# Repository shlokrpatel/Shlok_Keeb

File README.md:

# Shlok_Keeb
FOR SUBMISSION PURPOSES- here is the link to my project that I completely recorded with lapse- https://lapse.hackclub.com/user/@shlok_r_patel10

a custom keyboard I built myself. This includes the pcb, case, firmware, and eventually, the assembly. I built this to learn more on how to design pcb's and get better at CAD

Built as part of Hackclub's YSWS Keeb

# Features
Custom pcb made in kicad
MX switches
Qmk software
3d printed case
Individually lit rgbs for each key
Rotary Encoder
Oled Screen

# Why I build it
I love building things on my computer and seeing them come to life as I build it. I've been working at getting better at using CAD so whenever I have a chance to improve them with another skill I always take it. 

I was able to learn how to use Kicad, CAD, some firmware use, how to solder, and the engineering behind keyboard

# Design Process
I started in Kicad, I modeled the schematic with all my keys, leds, the microcontroller, oled, and rotary encoder. Then I moved to the actually pcb routing the traces, and placing the keys where i wanted them. After finished that I went to onshape to design the case in 2 peices that will be screwed or glued together. After that I went to the qmk software to write the firmware. 

# Components
Custom PCB
Raspberri pi pico
MX switches
Stabilizers
Usb cable
3D printed case
keycaps
Sk6812 Mini-e LEDs
EC11 rotary encoder
0.91in OLED display

# Challenges
My biggest challenges were:

Learned onshape 
routing my pcb with all the traces
building my case 
writing the firmware

# Images

Matrix schematic

PCB

Case

Bill of Materials(BOM)
| SI No. | Name | Notes | Quantity | Price/Unit (USD) | Total (USD) | Running Total (USD) | Link |
| --- | --- | --- | --- | --- | --- | --- | --- |
| 1 | 0.91" OLED Display | 128x32 I2C OLED, GND-VCC-SCL-SDA | 1 | $1.09 | $1.09 | $1.09 | https://www.aliexpress.us/item/2251832650376908.html |
| 2 | EC11 Rotary Encoder | ALPS EC11E compatible, vertical, H20mm | 1 | $0.46 | $0.46 | $1.55 | https://www.alibaba.com/product-detail/EC11-rotary-15-20mm-Meihua-Bing_1600985459709.html |
| 3 | Key Switches | MX compatible switches, pack of 10 | 7 | $1.00 | $7.00 | $8.55 | https://www.aliexpress.us/item/3256802192387196.html |
| 4 | SK6812MINI-E | Addressable RGB LED, LCSC C5149201 | 61 | $0.0649 | $3.96 | $12.51 | https://www.lcsc.com/product-detail/C5149201.html |
| 5 | 1N4148 Diodes | 1N4148, pack of 100 | 1 | $0.99 | $0.99 | $13.50 | https://www.aliexpress.com/w/wholesale-diode-1n4148.html |
| 6 | Durock V2 Screw-In Stabilizers | 5 stabilizers | 1 | $16.00 | $16.00 | $29.50 | https://upgradekeyboards.com/products/durock-v2-new-screw-in-stabilizers-clear |
| 7 | Custom PCB | JLCPCB manufactured PCB | 1 | $24.00 | $24.00 | $53.50 | https://jlcpcb.com/ |
| 8 | Thock King Shine Through Black PBT Keycap Set | Black pudding PBT, 61-key, RGB shine-through | 1 | $16.95 | $16.95 | $70.45 | https://www.thockking.com/products/shine-through-black-pbt-keycap-set-61-78-87-96-100-104-108 |
| 9 | Raspberry Pi Pico | RP2040 microcontroller | 1 | $4.00 | $4.00 | $74.45 | https://www.raspberrypi.com/products/raspberry-pi-pico/ |

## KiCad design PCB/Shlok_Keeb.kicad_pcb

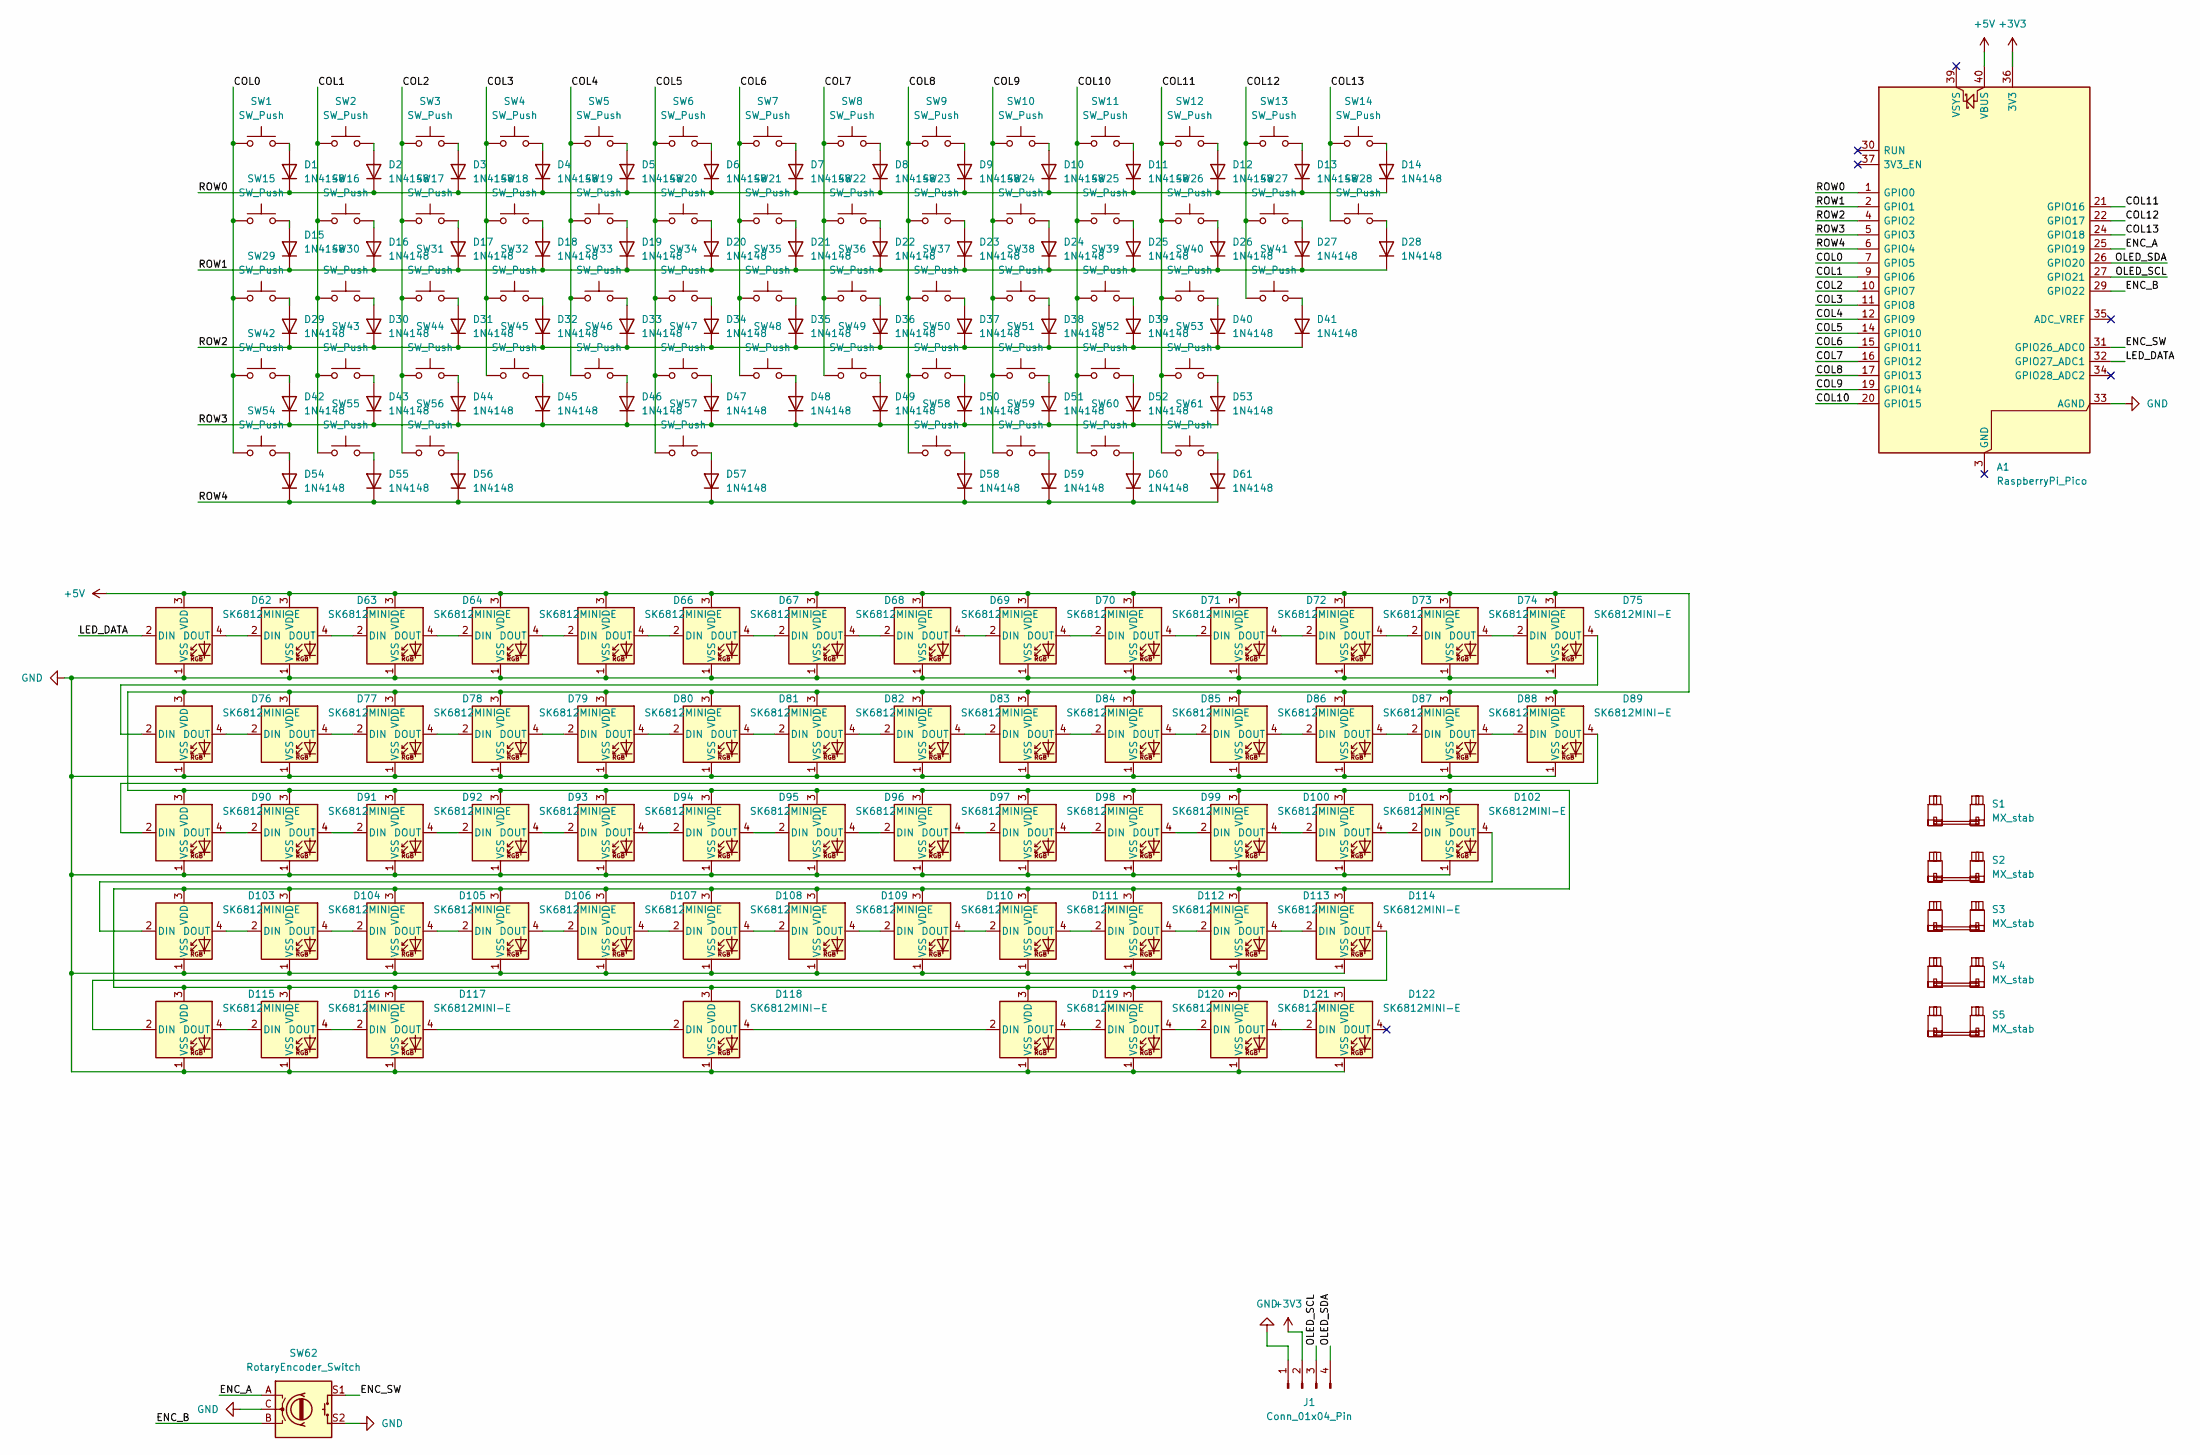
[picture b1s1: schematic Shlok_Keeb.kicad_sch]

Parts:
A1: RaspberryPi_Pico; RaspberryPi_Pico_Common_THT
D1, D2, D3, D4, D5, D6, D7, D8, D9, D10, D11, D12, D13, D14, D15, D16, D17, D18, D19, D20, D21, D22, D23, D24, D25, D26, D27, D28, D29, D30, D31, D32, D33, D34, D35, D36, D37, D38, D39, D40, D41, D42, D43, D44, D45, D46, D47, D48, D49, D50, D51, D52, D53, D54, D55, D56, D57, D58, D59, D60, D61: 1N4148; D_DO-35_SOD27_P7.62mm_Horizontal
D62, D63, D64, D65, D66, D67, D68, D69, D70, D71, D72, D73, D74, D75, D76, D77, D78, D79, D80, D81, D82, D83, D84, D85, D86, D87, D88, D89, D90, D91, D92, D93, D94, D95, D96, D97, D98, D99, D100, D101, D102, D103, D104, D105, D106, D107, D108, D109, D110, D111, D112, D113, D114, D115, D116, D117, D118, D119, D120, D121, D122: SK6812MINI-E; SK6812MINI-E_fixed
J1: Conn_01x04_Pin; ER_OLEDM0.91_1x-I2C
S1: MX_stab; STAB_MX_P_6.25u
S2, S3, S4, S5: MX_stab; STAB_MX_P_2u
SW1, SW2, SW3, SW4, SW5, SW6, SW7, SW8, SW9, SW10, SW11, SW12, SW13, SW14, SW15, SW16, SW17, SW18, SW19, SW20, SW21, SW22, SW23, SW24, SW25, SW26, SW27, SW28, SW29, SW30, SW31, SW32, SW33, SW34, SW35, SW36, SW37, SW38, SW39, SW40, SW41, SW42, SW43, SW44, SW45, SW46, SW47, SW48, SW49, SW50, SW51, SW52, SW53, SW54, SW55, SW56, SW57, SW58, SW59, SW60, SW61: SW_Push; SW_MX_1u
SW62: RotaryEncoder_Switch; RotaryEncoder_Alps_EC11E-Switch_Vertical_H20mm

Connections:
+3V3: A1.36 (3V3), J1.2
+5V: A1.40 (VBUS), D62.3 (VDD), D63.3 (VDD), D64.3 (VDD), D65.3 (VDD), D66.3 (VDD), D67.3 (VDD), D68.3 (VDD), D69.3 (VDD), D70.3 (VDD), D71.3 (VDD), D72.3 (VDD), D73.3 (VDD), D74.3 (VDD), D75.3 (VDD), D76.3 (VDD), D77.3 (VDD), D78.3 (VDD), D79.3 (VDD), D80.3 (VDD), D81.3 (VDD), D82.3 (VDD), D83.3 (VDD), D84.3 (VDD), D85.3 (VDD), D86.3 (VDD), D87.3 (VDD), D88.3 (VDD), D89.3 (VDD), D90.3 (VDD), D91.3 (VDD), D92.3 (VDD), D93.3 (VDD), D94.3 (VDD), D95.3 (VDD), D96.3 (VDD), D97.3 (VDD), D98.3 (VDD), D99.3 (VDD), D100.3 (VDD), D101.3 (VDD), D102.3 (VDD), D103.3 (VDD), D104.3 (VDD), D105.3 (VDD), D106.3 (VDD), D107.3 (VDD), D108.3 (VDD), D109.3 (VDD), D110.3 (VDD), D111.3 (VDD), D112.3 (VDD), D113.3 (VDD), D114.3 (VDD), D115.3 (VDD), D116.3 (VDD), D117.3 (VDD), D118.3 (VDD), D119.3 (VDD), D120.3 (VDD), D121.3 (VDD), D122.3 (VDD)
/COL0: A1.7 (GPIO5), SW1.1, SW15.1, SW29.1, SW42.1, SW54.1
/COL1: A1.9 (GPIO6), SW2.1, SW16.1, SW30.1, SW43.1, SW55.1
/COL2: A1.10 (GPIO7), SW3.1, SW17.1, SW31.1, SW44.1, SW56.1
/COL3: A1.11 (GPIO8), SW4.1, SW18.1, SW32.1, SW45.1
/COL4: A1.12 (GPIO9), SW5.1, SW19.1, SW33.1, SW46.1
/COL5: A1.14 (GPIO10), SW6.1, SW20.1, SW34.1, SW47.1, SW57.1
/COL6: A1.15 (GPIO11), SW7.1, SW21.1, SW35.1, SW48.1
/COL7: A1.16 (GPIO12), SW8.1, SW22.1, SW36.1, SW49.1
/COL8: A1.17 (GPIO13), SW9.1, SW23.1, SW37.1, SW50.1, SW58.1
/COL9: A1.19 (GPIO14), SW10.1, SW24.1, SW38.1, SW51.1, SW59.1
/COL10: A1.20 (GPIO15), SW11.1, SW25.1, SW39.1, SW52.1, SW60.1
/COL11: A1.21 (GPIO16), SW12.1, SW26.1, SW40.1, SW53.1, SW61.1
/COL12: A1.22 (GPIO17), SW13.1, SW27.1, SW41.1
/COL13: A1.24 (GPIO18), SW14.1, SW28.1
/ENC_A: A1.25 (GPIO19), SW62.A
/ENC_B: A1.29 (GPIO22), SW62.B
/ENC_SW: A1.31 (GPIO26_ADC0), SW62.S1
/LED_DATA: A1.32 (GPIO27_ADC1), D62.2 (DIN)
/OLED_SCL: A1.27 (GPIO21), J1.3
/OLED_SDA: A1.26 (GPIO20), J1.4
/ROW0: A1.1 (GPIO0), D1.1 (K), D2.1 (K), D3.1 (K), D4.1 (K), D5.1 (K), D6.1 (K), D7.1 (K), D8.1 (K), D9.1 (K), D10.1 (K), D11.1 (K), D12.1 (K), D13.1 (K), D14.1 (K)
/ROW1: A1.2 (GPIO1), D15.1 (K), D16.1 (K), D17.1 (K), D18.1 (K), D19.1 (K), D20.1 (K), D21.1 (K), D22.1 (K), D23.1 (K), D24.1 (K), D25.1 (K), D26.1 (K), D27.1 (K), D28.1 (K)
/ROW2: A1.4 (GPIO2), D29.1 (K), D30.1 (K), D31.1 (K), D32.1 (K), D33.1 (K), D34.1 (K), D35.1 (K), D36.1 (K), D37.1 (K), D38.1 (K), D39.1 (K), D40.1 (K), D41.1 (K)
/ROW3: A1.5 (GPIO3), D42.1 (K), D43.1 (K), D44.1 (K), D45.1 (K), D46.1 (K), D47.1 (K), D48.1 (K), D49.1 (K), D50.1 (K), D51.1 (K), D52.1 (K), D53.1 (K)
/ROW4: A1.6 (GPIO4), D54.1 (K), D55.1 (K), D56.1 (K), D57.1 (K), D58.1 (K), D59.1 (K), D60.1 (K), D61.1 (K)
GND: A1.33 (AGND), D62.1 (VSS), D63.1 (VSS), D64.1 (VSS), D65.1 (VSS), D66.1 (VSS), D67.1 (VSS), D68.1 (VSS), D69.1 (VSS), D70.1 (VSS), D71.1 (VSS), D72.1 (VSS), D73.1 (VSS), D74.1 (VSS), D75.1 (VSS), D76.1 (VSS), D77.1 (VSS), D78.1 (VSS), D79.1 (VSS), D80.1 (VSS), D81.1 (VSS), D82.1 (VSS), D83.1 (VSS), D84.1 (VSS), D85.1 (VSS), D86.1 (VSS), D87.1 (VSS), D88.1 (VSS), D89.1 (VSS), D90.1 (VSS), D91.1 (VSS), D92.1 (VSS), D93.1 (VSS), D94.1 (VSS), D95.1 (VSS), D96.1 (VSS), D97.1 (VSS), D98.1 (VSS), D99.1 (VSS), D100.1 (VSS), D101.1 (VSS), D102.1 (VSS), D103.1 (VSS), D104.1 (VSS), D105.1 (VSS), D106.1 (VSS), D107.1 (VSS), D108.1 (VSS), D109.1 (VSS), D110.1 (VSS), D111.1 (VSS), D112.1 (VSS), D113.1 (VSS), D114.1 (VSS), D115.1 (VSS), D116.1 (VSS), D117.1 (VSS), D118.1 (VSS), D119.1 (VSS), D120.1 (VSS), D121.1 (VSS), D122.1 (VSS), J1.1, SW62.C, SW62.S2
unnamed: D1.2 (A), SW1.2
unnamed: D2.2 (A), SW2.2
unnamed: D3.2 (A), SW3.2
unnamed: D4.2 (A), SW4.2
unnamed: D5.2 (A), SW5.2
unnamed: D6.2 (A), SW6.2
unnamed: D7.2 (A), SW7.2
unnamed: D8.2 (A), SW8.2
unnamed: D9.2 (A), SW9.2
unnamed: D10.2 (A), SW10.2
unnamed: D11.2 (A), SW11.2
unnamed: D12.2 (A), SW12.2
unnamed: D13.2 (A), SW13.2
unnamed: D14.2 (A), SW14.2
unnamed: D15.2 (A), SW15.2
unnamed: D16.2 (A), SW16.2
unnamed: D17.2 (A), SW17.2
unnamed: D18.2 (A), SW18.2
unnamed: D19.2 (A), SW19.2
unnamed: D20.2 (A), SW20.2
unnamed: D21.2 (A), SW21.2
unnamed: D22.2 (A), SW22.2
unnamed: D23.2 (A), SW23.2
unnamed: D24.2 (A), SW24.2
unnamed: D25.2 (A), SW25.2
unnamed: D26.2 (A), SW26.2
unnamed: D27.2 (A), SW27.2
unnamed: D28.2 (A), SW28.2
unnamed: D29.2 (A), SW29.2
unnamed: D30.2 (A), SW30.2
unnamed: D31.2 (A), SW31.2
unnamed: D32.2 (A), SW32.2
unnamed: D33.2 (A), SW33.2
unnamed: D34.2 (A), SW34.2
unnamed: D35.2 (A), SW35.2
unnamed: D36.2 (A), SW36.2
unnamed: D37.2 (A), SW37.2
unnamed: D38.2 (A), SW38.2
unnamed: D39.2 (A), SW39.2
unnamed: D40.2 (A), SW40.2
unnamed: D41.2 (A), SW41.2
unnamed: D42.2 (A), SW42.2
unnamed: D43.2 (A), SW43.2
unnamed: D44.2 (A), SW44.2
unnamed: D45.2 (A), SW45.2
unnamed: D46.2 (A), SW46.2
unnamed: D47.2 (A), SW47.2
unnamed: D48.2 (A), SW48.2
unnamed: D49.2 (A), SW49.2
unnamed: D50.2 (A), SW50.2
unnamed: D51.2 (A), SW51.2
unnamed: D52.2 (A), SW52.2
unnamed: D53.2 (A), SW53.2
unnamed: D54.2 (A), SW54.2
unnamed: D55.2 (A), SW55.2
unnamed: D56.2 (A), SW56.2
unnamed: D57.2 (A), SW57.2
unnamed: D58.2 (A), SW58.2
unnamed: D59.2 (A), SW59.2
unnamed: D60.2 (A), SW60.2
unnamed: D61.2 (A), SW61.2
unnamed: D62.4 (DOUT), D63.2 (DIN)
unnamed: D63.4 (DOUT), D64.2 (DIN)
unnamed: D64.4 (DOUT), D65.2 (DIN)
unnamed: D65.4 (DOUT), D66.2 (DIN)
unnamed: D66.4 (DOUT), D67.2 (DIN)
unnamed: D67.4 (DOUT), D68.2 (DIN)
unnamed: D68.4 (DOUT), D69.2 (DIN)
unnamed: D69.4 (DOUT), D70.2 (DIN)
unnamed: D70.4 (DOUT), D71.2 (DIN)
unnamed: D71.4 (DOUT), D72.2 (DIN)
unnamed: D72.4 (DOUT), D73.2 (DIN)
unnamed: D73.4 (DOUT), D74.2 (DIN)
unnamed: D74.4 (DOUT), D75.2 (DIN)
unnamed: D75.4 (DOUT), D76.2 (DIN)
unnamed: D76.4 (DOUT), D77.2 (DIN)
unnamed: D77.4 (DOUT), D78.2 (DIN)
unnamed: D78.4 (DOUT), D79.2 (DIN)
unnamed: D79.4 (DOUT), D80.2 (DIN)
unnamed: D80.4 (DOUT), D81.2 (DIN)
unnamed: D81.4 (DOUT), D82.2 (DIN)
unnamed: D82.4 (DOUT), D83.2 (DIN)
unnamed: D83.4 (DOUT), D84.2 (DIN)
unnamed: D84.4 (DOUT), D85.2 (DIN)
unnamed: D85.4 (DOUT), D86.2 (DIN)
unnamed: D86.4 (DOUT), D87.2 (DIN)
unnamed: D87.4 (DOUT), D88.2 (DIN)
unnamed: D88.4 (DOUT), D89.2 (DIN)
unnamed: D89.4 (DOUT), D90.2 (DIN)
unnamed: D90.4 (DOUT), D91.2 (DIN)
unnamed: D91.4 (DOUT), D92.2 (DIN)
unnamed: D92.4 (DOUT), D93.2 (DIN)
unnamed: D93.4 (DOUT), D94.2 (DIN)
unnamed: D94.4 (DOUT), D95.2 (DIN)
unnamed: D95.4 (DOUT), D96.2 (DIN)
unnamed: D96.4 (DOUT), D97.2 (DIN)
unnamed: D97.4 (DOUT), D98.2 (DIN)
unnamed: D98.4 (DOUT), D99.2 (DIN)
unnamed: D99.4 (DOUT), D100.2 (DIN)
unnamed: D100.4 (DOUT), D101.2 (DIN)
unnamed: D101.4 (DOUT), D102.2 (DIN)
unnamed: D102.4 (DOUT), D103.2 (DIN)
unnamed: D103.4 (DOUT), D104.2 (DIN)
unnamed: D104.4 (DOUT), D105.2 (DIN)
unnamed: D105.4 (DOUT), D106.2 (DIN)
unnamed: D106.4 (DOUT), D107.2 (DIN)
unnamed: D107.4 (DOUT), D108.2 (DIN)
unnamed: D108.4 (DOUT), D109.2 (DIN)
unnamed: D109.4 (DOUT), D110.2 (DIN)
unnamed: D110.4 (DOUT), D111.2 (DIN)
unnamed: D111.4 (DOUT), D112.2 (DIN)
unnamed: D112.4 (DOUT), D113.2 (DIN)
unnamed: D113.4 (DOUT), D114.2 (DIN)
unnamed: D114.4 (DOUT), D115.2 (DIN)
unnamed: D115.4 (DOUT), D116.2 (DIN)
unnamed: D116.4 (DOUT), D117.2 (DIN)
unnamed: D117.4 (DOUT), D118.2 (DIN)
unnamed: D118.4 (DOUT), D119.2 (DIN)
unnamed: D119.4 (DOUT), D120.2 (DIN)
unnamed: D120.4 (DOUT), D121.2 (DIN)
unnamed: D121.4 (DOUT), D122.2 (DIN)

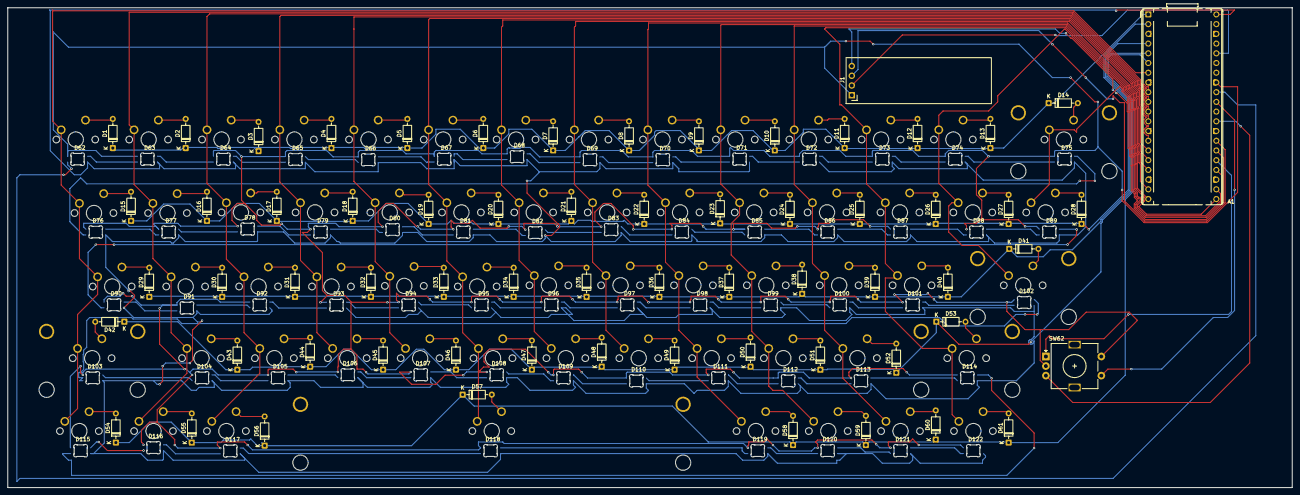
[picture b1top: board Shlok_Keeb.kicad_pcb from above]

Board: 2 copper layers, 335.7 x 125.4 mm, 191 parts (0 on the bottom side), 149 nets.
